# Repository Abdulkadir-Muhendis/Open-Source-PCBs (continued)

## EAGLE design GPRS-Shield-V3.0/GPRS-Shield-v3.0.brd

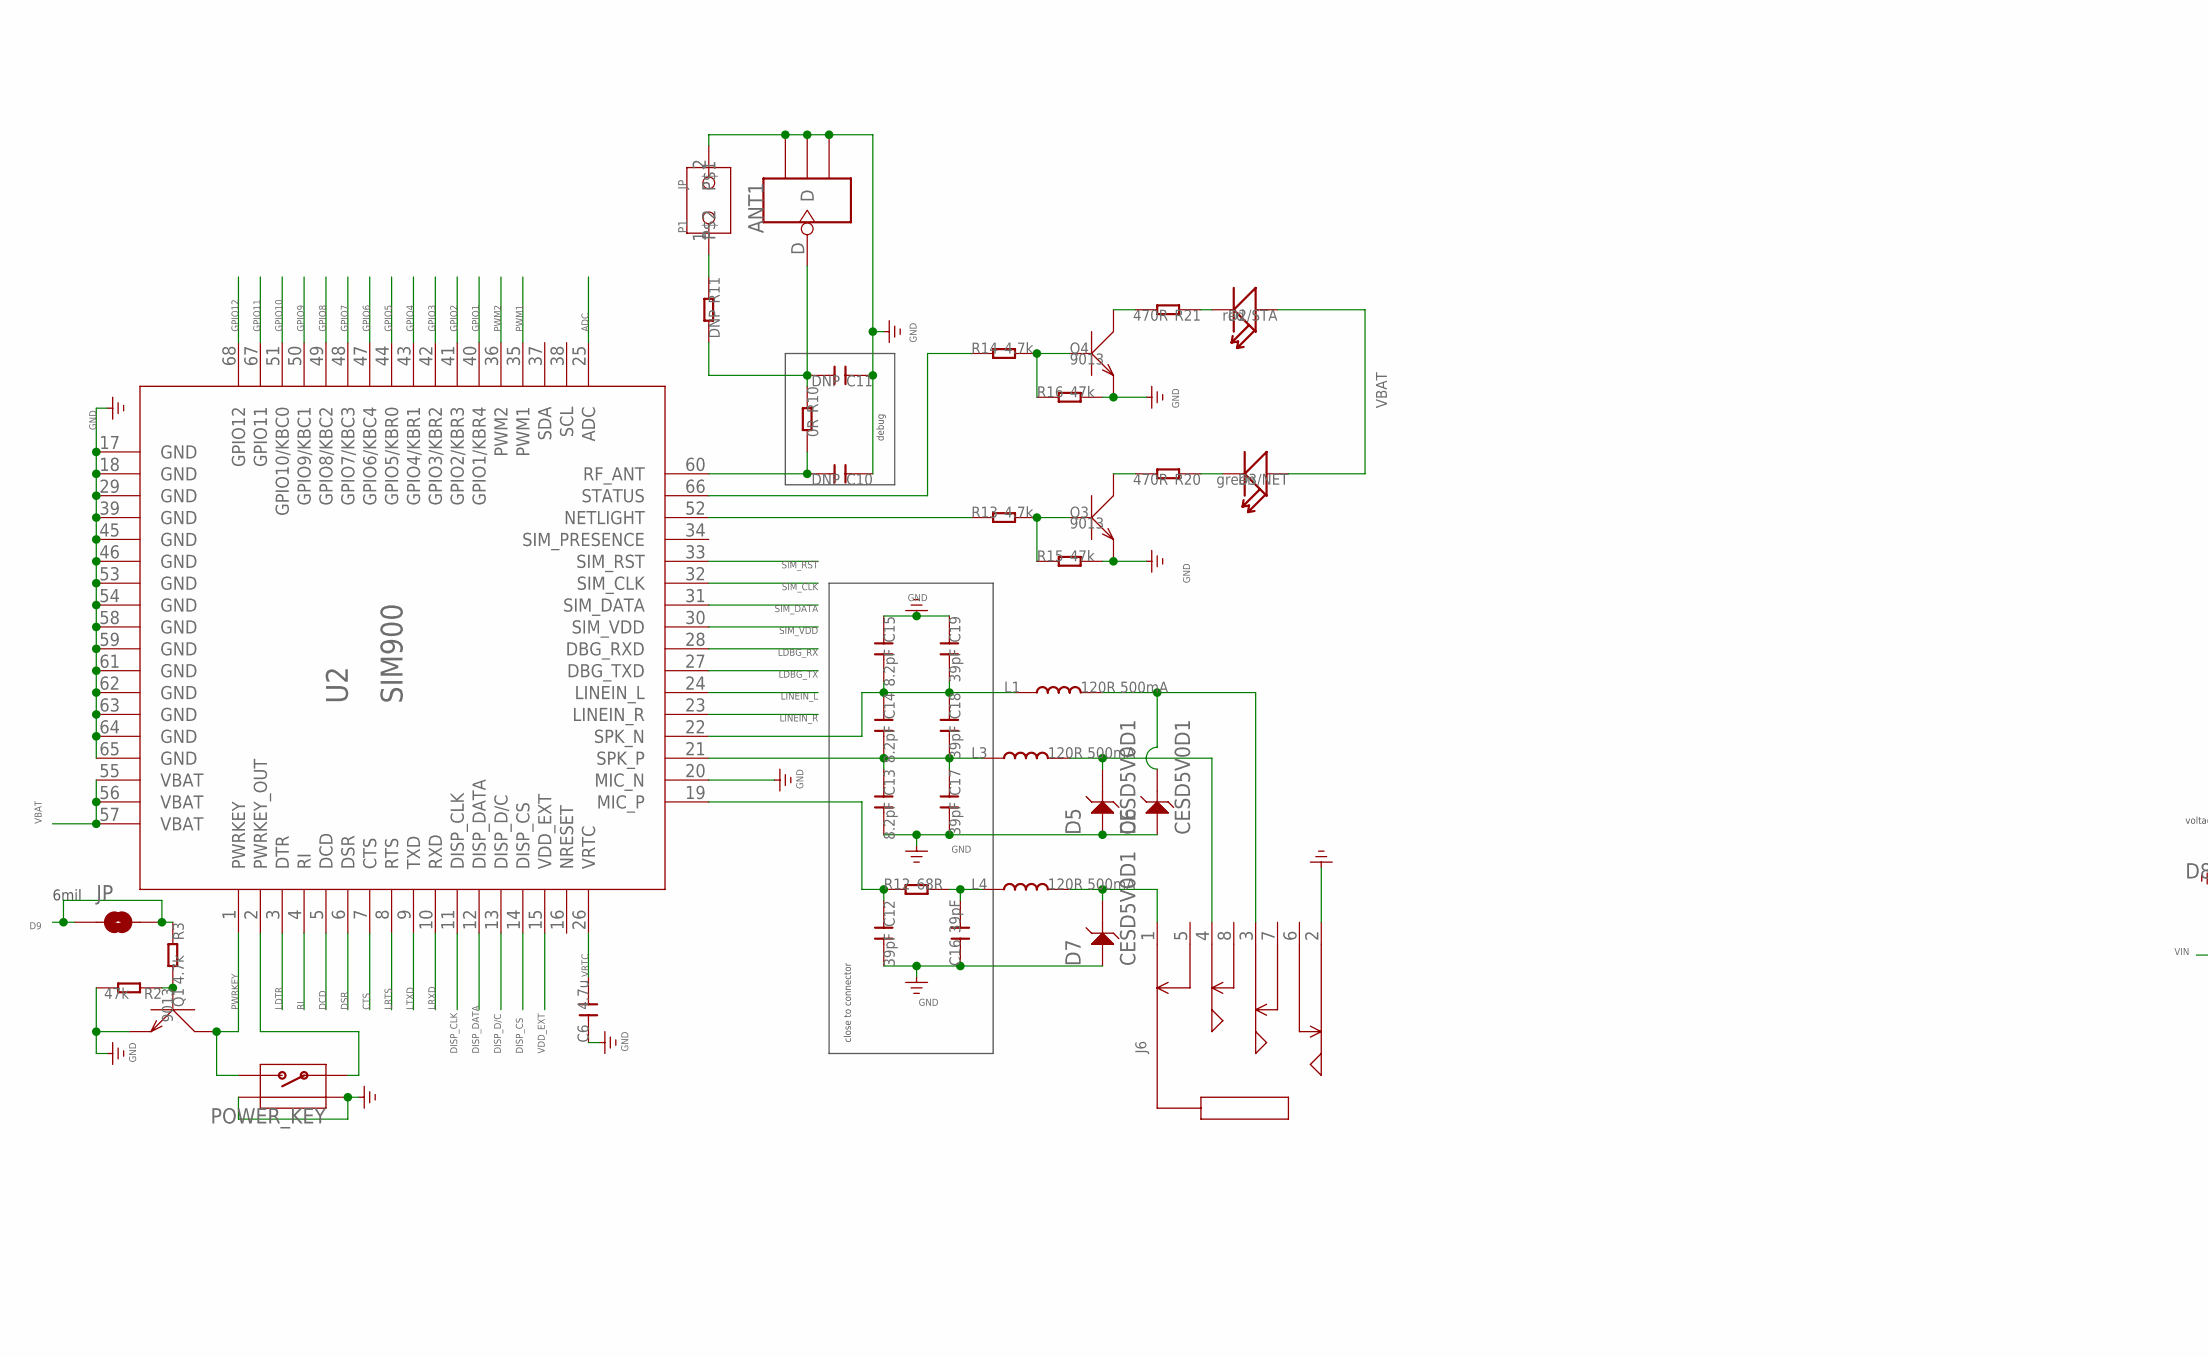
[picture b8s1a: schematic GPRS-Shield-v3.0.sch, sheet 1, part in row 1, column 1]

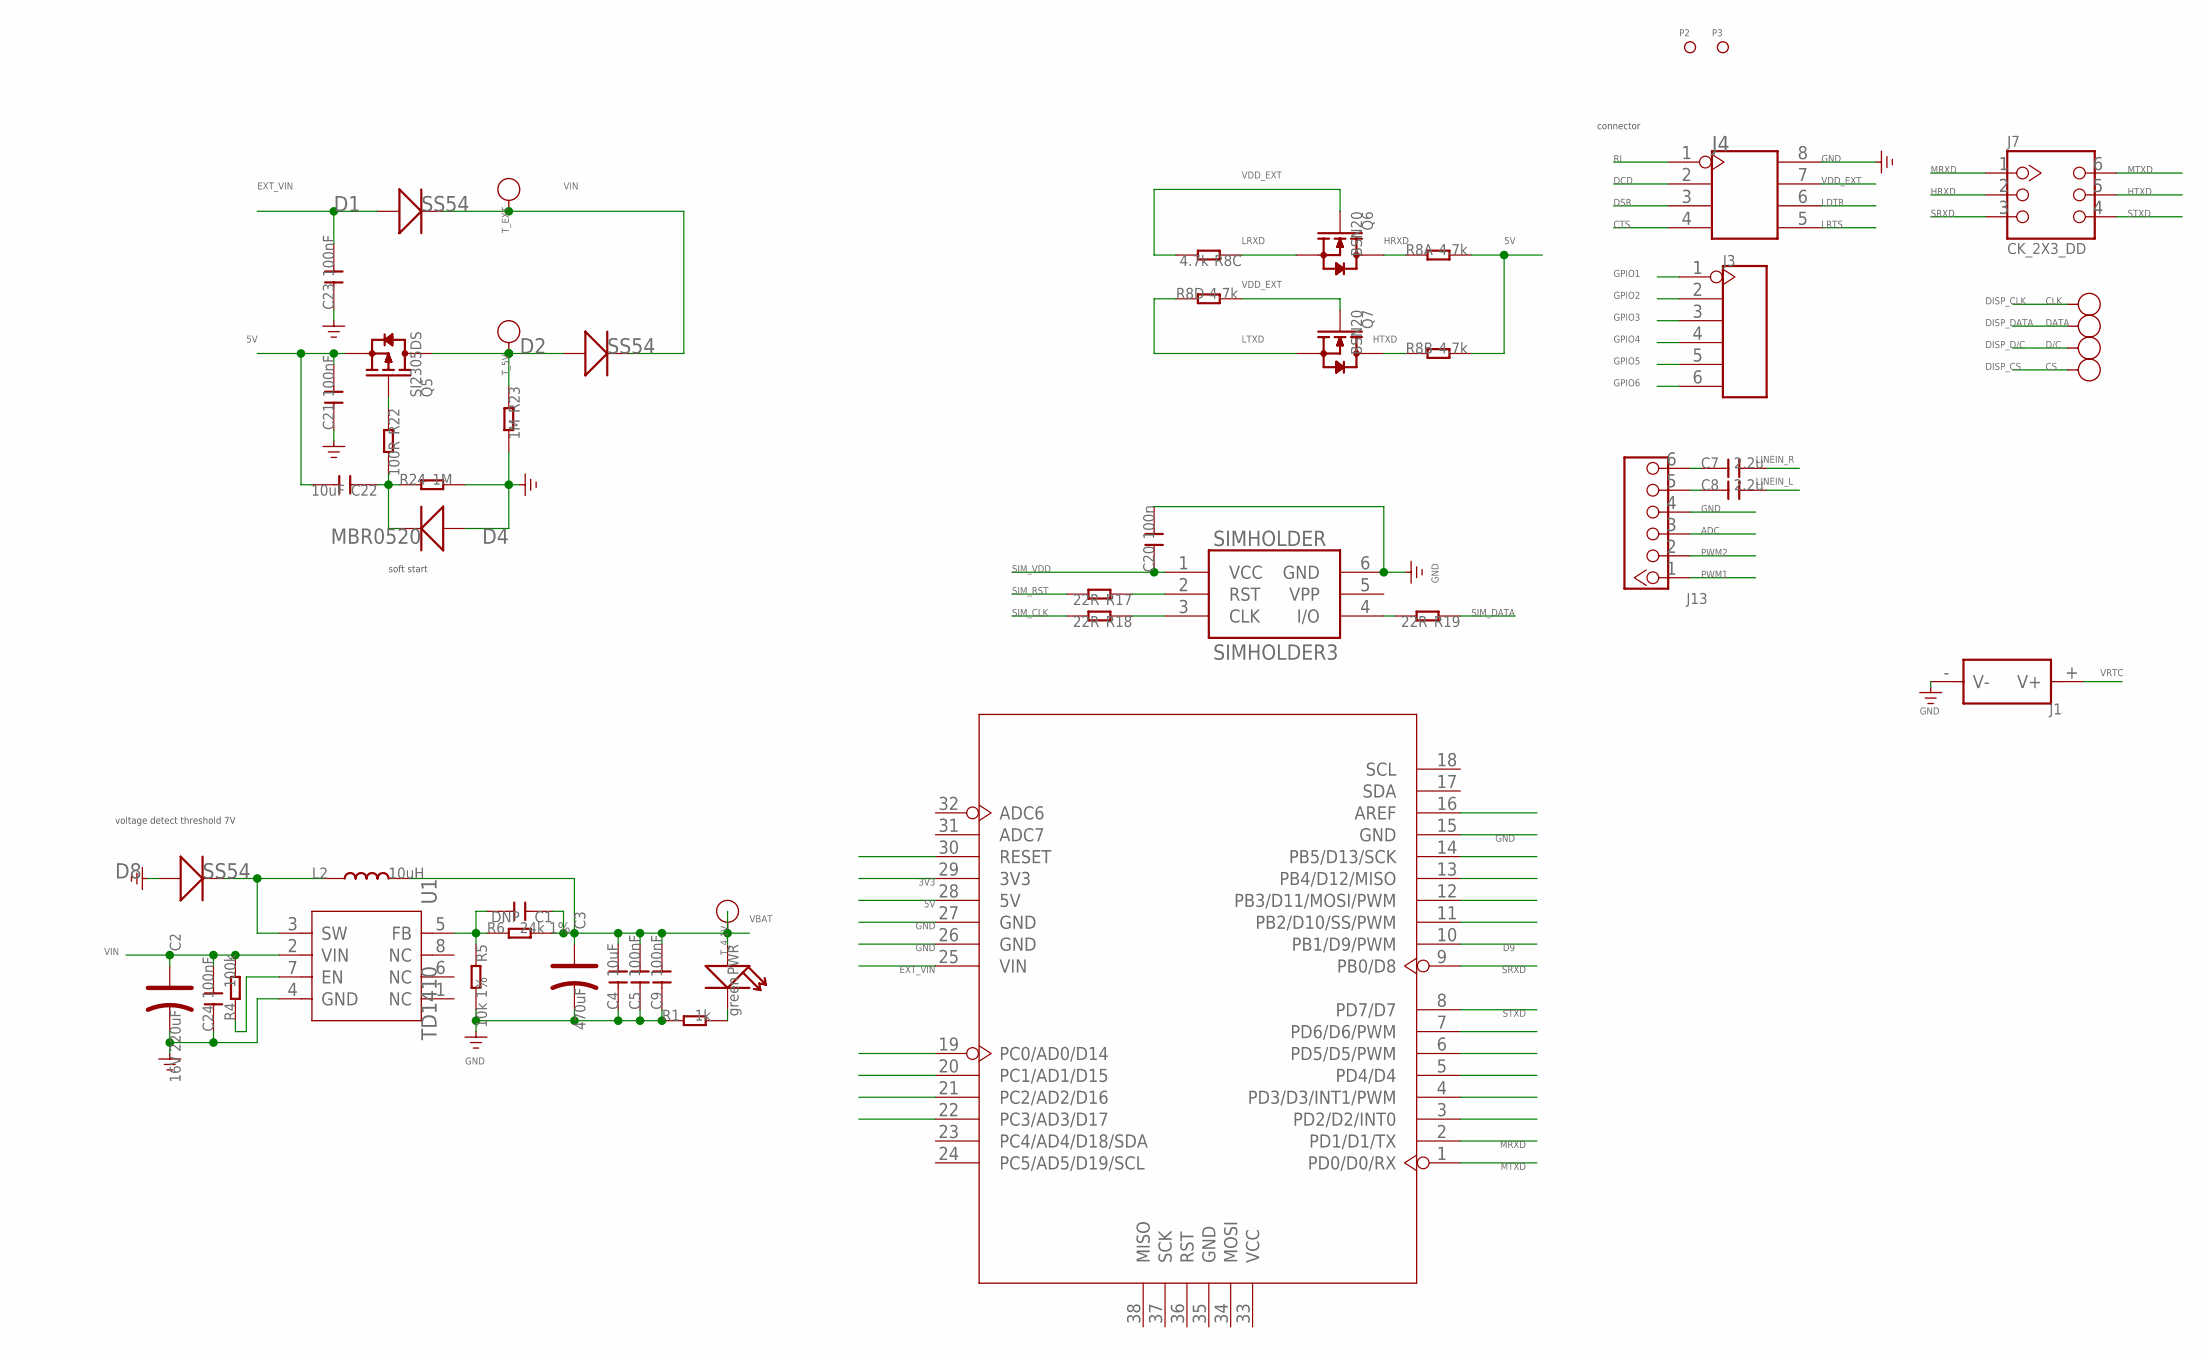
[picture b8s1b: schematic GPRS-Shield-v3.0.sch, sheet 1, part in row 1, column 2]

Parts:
ANT1: ANTENNA-U-FL; 4P-U-FL
C1, C10, C11: DNP; C0603
C2: 16V 220uF; ELECTRO-SMD-D-5.6MM
C3: 470uF; AVX-D
C4, C22: 10uF; C0805
C5, C9, C21, C23, C24: 100nF; C0603
C6: 4.7u; C0805
C7, C8: 2.2u; C0805
C12, C16, C17, C18, C19: 39pF; C0603
C13, C14, C15: 8.2pF; C0603
C20: 100n; C0603
CLK: PAD-TEST-POINT-CIRCLE'4545'; TP_4545
CS: PAD-TEST-POINT-CIRCLE'4545'; TP_4545
D1, D2, D8: SS54; SMB
D2/STA: red; LED-0603
D3/NET: green; LED-0603
D4: MBR0520; SOD123-2.7X1.6
D5, D6, D7: CESD5V0D1; SOD123-2.7X1.6
D/C: PAD-TEST-POINT-CIRCLE'4545'; TP_4545
DATA: PAD-TEST-POINT-CIRCLE'4545'; TP_4545
J1: HOLDER-BAT; SMD-CR1220-2
J3: HEADER-6P-65/35MIL; 6P-2.54-65/35MIL
J4: HEADER-2X4P-2.54; 2X4P-2.54
J6: AUDIO-JACK-3.5'PJ-393'; 8P-SMD-3.5
J7: CK_2X3_DD; CK_2X3
J13: HEADER_1X6; CK_1X6
JP: PAD-SOLDERJUMPERNC; 2P-SMD-3.3X2
L1, L3, L4: 120R 500mA; L0603
L2: 10uH; L0630
P1: JP
P2, P3: PAD-MARK; ROUND-MARK-1.0
POWER_KEY: BUTTON-4P-REINFORCE'TS-118E'; 4P-SMD-7X3.5X3.5H
PWR: green; D0603
Q1, Q3, Q4: 9013; SOT23
Q5: SI2305DS; SOT23
Q6, Q7: BSN20; SOT23
R1: 1k; R0603
R2, R15, R16: 47k; R0603
R3, R13, R14: 4.7k; R0603
R4: 100k; R0603
R5: 10k 1%; R0603
R6: 24k 1%; R0603
R8: 4.7k; 1206-8-3.3X2.4
R10: 0R; R0603
R11: DNP; R0603
R12: 68R; R0603
R17, R18, R19: 22R; R0603
R20, R21: 470R; R0603
R22: 100R; R0603
R23, R24: 1M; R0603
SIMHOLDER: SIMHOLDER3
T_4.1V, T_5V: PAD-TEST-POINT-CIRCLE'4545'; TP_4545; PARTNO DNP
T_EXT: PAD-TEST-POINT-CIRCLE'4545'; TP_4545; PARTNO DNP
U1: TD1410; SOP8
U2: SIM900
U4: ARDUINO-38P'WITH/O-SILK'; ARDUINO-38P-500519002

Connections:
3V3: U4.29 (3V3)
5V: C21.2, C22.2, Q5.2 (S), R8.7 (2), R8.8 (2), U4.28 (5V)
ADC: J13.3, U2.25 (ADC)
CTS: J4.4, U2.7 (CTS)
D9: JP.1, JP.2, R3.1, U4.10 (PB1/D9/PWM)
DCD: J4.2, U2.5 (DCD)
DISP_CLK: CLK.T, U2.11 (DISP_CLK)
DISP_CS: CS.T, U2.14 (DISP_CS)
DISP_D/C: D/C.T, U2.13 (DISP_D/C)
DISP_DATA: DATA.T, U2.12 (DISP_DATA)
DSR: J4.3, U2.6 (DSR)
EXT_VIN: C23.2, D1.+, U4.25 (VIN)
GND: ANT1.GND1, ANT1.GND2, ANT1.GND3, C2.-, C3.-, C4.1, C5.1, C6.1, C9.1, C10.1, C11.1, C12.2, C13.2, C15.1, C16.1, C17.2, C19.1, C20.2, C21.1, C23.1, C24.1, D4.1 (+), D5.1, D6.1, D7.1, D8.+, J1.- (V-), J4.8, J6.2, J13.4, P1.2, POWER_KEY.S1, POWER_KEY.S2, Q1.2 (E), Q3.2 (E), Q4.2 (E), R1.1, R2.2, R5.2, R15.2, R16.2, R23.2, R24.2, SIMHOLDER.6 (GND), U1.4 (GND), U2.17 (GND), U2.18 (GND), U2.20 (MIC_N), U2.29 (GND), U2.39 (GND), U2.45 (GND), U2.46 (GND), U2.53 (GND), U2.54 (GND), U2.58 (GND), U2.59 (GND), U2.61 (GND), U2.62 (GND), U2.63 (GND), U2.64 (GND), U2.65 (GND), U4.15 (GND), U4.26 (GND), U4.27 (GND)
GPIO1: J3.1, U2.40 (GPIO1/KBR4)
GPIO2: J3.2, U2.41 (GPIO2/KBR3)
GPIO3: J3.3, U2.42 (GPIO3/KBR2)
GPIO4: J3.4, U2.43 (GPIO4/KBR1)
GPIO5: J3.5, U2.44 (GPIO5/KBR0)
GPIO6: J3.6, U2.47 (GPIO6/KBC4)
GPIO7: U2.48 (GPIO7/KBC3)
GPIO8: U2.49 (GPIO8/KBC2)
GPIO9: U2.50 (GPIO9/KBC1)
GPIO10: U2.51 (GPIO10/KBC0)
GPIO11: U2.67 (GPIO11)
GPIO12: U2.68 (GPIO12)
HRXD: J7.2, Q6.3 (D), R8.1
HTXD: J7.5, Q7.3 (D), R8.2 (1)
LDBG_RX: U2.28 (DBG_RXD)
LDBG_TX: U2.27 (DBG_TXD)
LDTR: J4.6, U2.3 (DTR)
LINEIN_L: C8.2, U2.24 (LINEIN_L)
LINEIN_R: C7.2, U2.23 (LINEIN_R)
LRTS: J4.5, U2.8 (RTS)
LRXD: Q6.2 (S), R8.3 (1), U2.10 (RXD)
LTXD: Q7.2 (S), R8.4 (1), U2.9 (TXD)
MRXD: J7.1, U4.2 (PD1/D1/TX)
MTXD: J7.6, U4.1 (PD0/D0/RX)
unnamed: C10.2, R10.2, U2.60 (RF_ANT)
unnamed: D2.+, Q5.3 (D), R23.1, T_5V.T
unnamed: Q3.3 (C), R20.2
unnamed: R19.2, SIMHOLDER.4 (I/O)
unnamed: R18.1, SIMHOLDER.3 (CLK)
unnamed: R17.1, SIMHOLDER.2 (RST)
unnamed: D3/NET.-, R20.1
unnamed: Q3.1 (B), R13.2, R15.1
unnamed: PWR.-, R1.2
unnamed: R13.1, U2.52 (NETLIGHT)
unnamed: POWER_KEY.1, U2.2 (PWRKEY_OUT)
unnamed: R4.1, U1.7 (EN)
unnamed: C12.1, R12.1, U2.19 (MIC_P)
unnamed: C13.1, C14.2, C17.1, C18.2, L3.1, U2.21 (SPK_P)
unnamed: Q4.3 (C), R21.2
unnamed: D2/STA.-, R21.1
unnamed: Q4.1 (B), R14.2, R16.1
unnamed: C14.1, C15.2, C18.1, C19.2, L1.1, U2.22 (SPK_N)
unnamed: R14.1, U2.66 (STATUS)
unnamed: ANT1.D, C11.2, R10.1, R11.2
unnamed: C7.1, J13.6
unnamed: C8.1, J13.5
unnamed: C16.2, L4.1, R12.2
unnamed: Q5.1 (G), R22.1
unnamed: Q1.1 (B), R2.1, R3.2
unnamed: D8.-, L2.1, U1.3 (SW)
unnamed: C22.1, D4.2 (-), R22.2, R24.1
unnamed: D7.2, J6.1, L4.2
unnamed: C1.2, R5.1, R6.1, U1.5 (FB)
unnamed: D5.2, J6.4, L3.2
unnamed: D6.2, J6.3, L1.2
unnamed: P1.1, R11.1
PWM1: J13.1, U2.35 (PWM1)
PWM2: J13.2, U2.36 (PWM2)
PWRKEY: POWER_KEY.2, Q1.3 (C), U2.1 (PWRKEY)
RI: J4.1, U2.4 (RI)
SIM_CLK: R18.2, U2.32 (SIM_CLK)
SIM_DATA: R19.1, U2.31 (SIM_DATA)
SIM_RST: R17.2, U2.33 (SIM_RST)
SIM_VDD: C20.1, SIMHOLDER.1 (VCC), U2.30 (SIM_VDD)
SRXD: J7.3, U4.9 (PB0/D8)
STXD: J7.4, U4.8 (PD7/D7)
VBAT: C1.1, C3.+, C4.2, C5.2, C9.2, D2/STA.+, D3/NET.+, L2.2, PWR.+, R6.2, T_4.1V.T, U2.55 (VBAT), U2.56 (VBAT), U2.57 (VBAT)
VDD_EXT: J4.7, Q6.1 (G), Q7.1 (G), R8.5 (2), R8.6 (2), U2.15 (VDD_EXT)
VIN: C2.+, C24.2, D1.-, D2.-, R4.2, T_EXT.T, U1.2 (VIN)
VRTC: C6.2, J1.+ (V+), U2.26 (VRTC)

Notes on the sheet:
close to connector
debug
soft start
voltage detect threshold 7V
connector
6mil

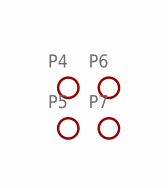
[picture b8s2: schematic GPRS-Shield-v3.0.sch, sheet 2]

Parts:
P4, P5, P6, P7: PAD-MARK; ROUND-MARK-1.0

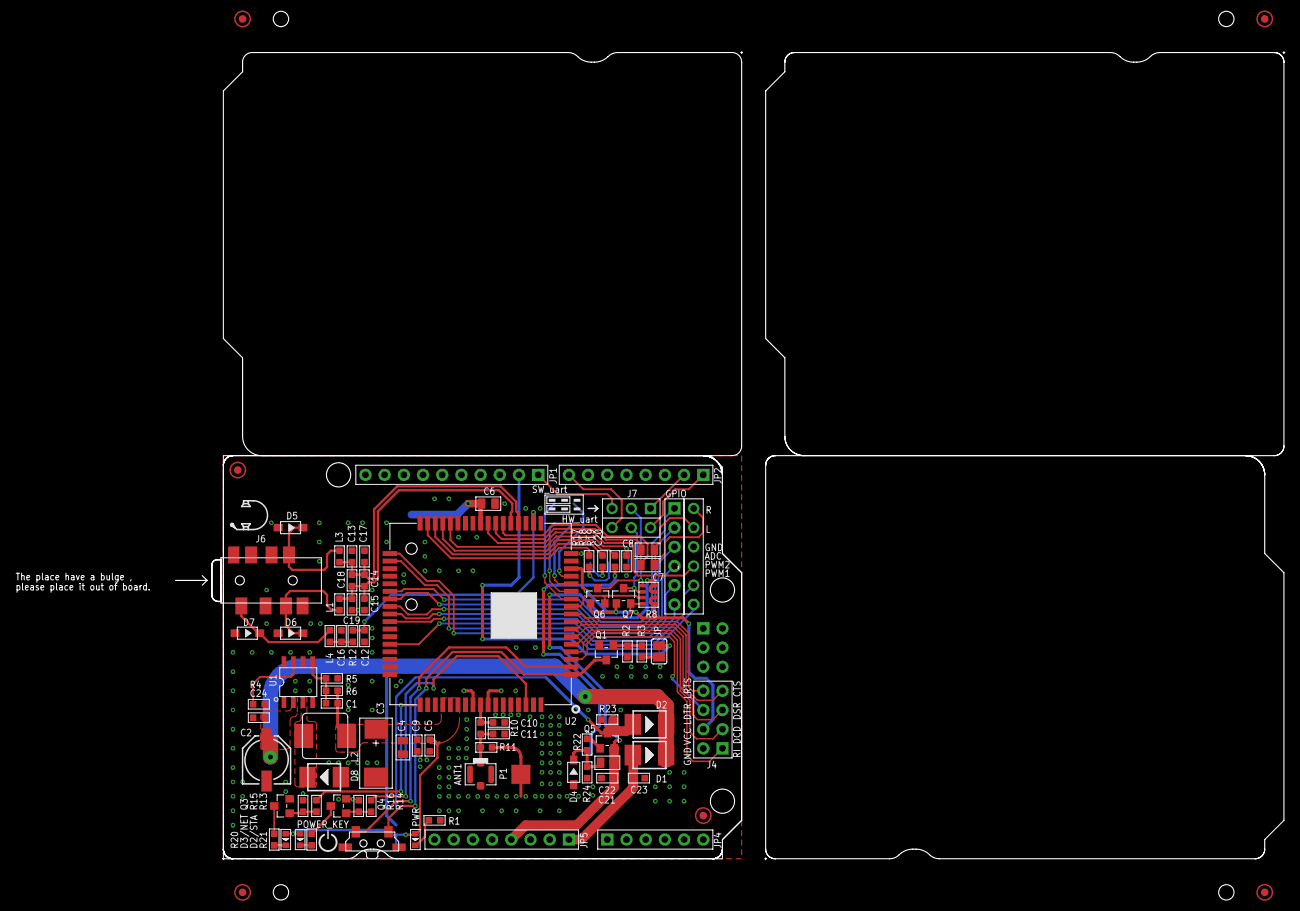
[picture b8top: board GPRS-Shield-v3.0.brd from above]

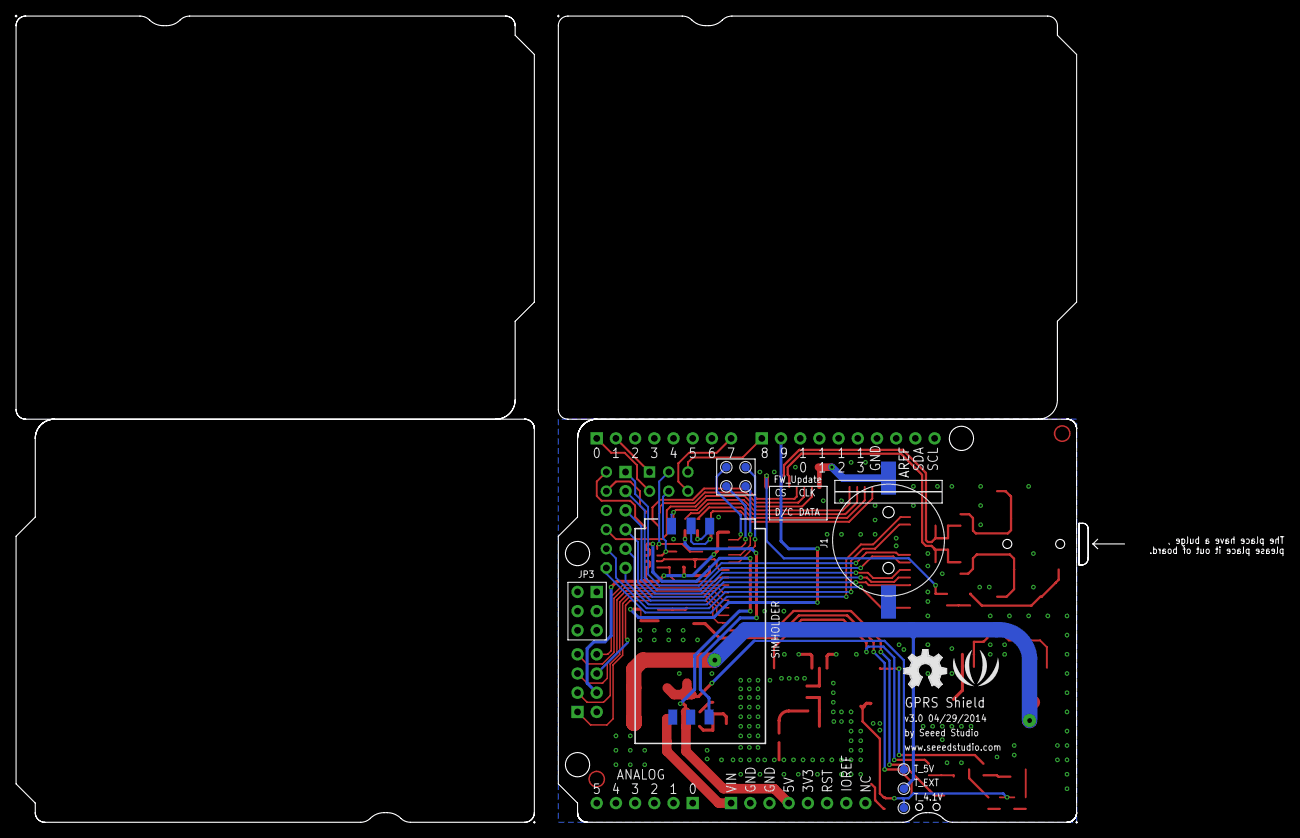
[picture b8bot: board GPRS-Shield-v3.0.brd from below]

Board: 2 copper layers, 146.8 x 106.9 mm, 95 parts (11 on the bottom side), 74 nets.

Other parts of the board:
U$26: LOGO_SILK
U$28: OSHW_FILLX200_NOTEXT
